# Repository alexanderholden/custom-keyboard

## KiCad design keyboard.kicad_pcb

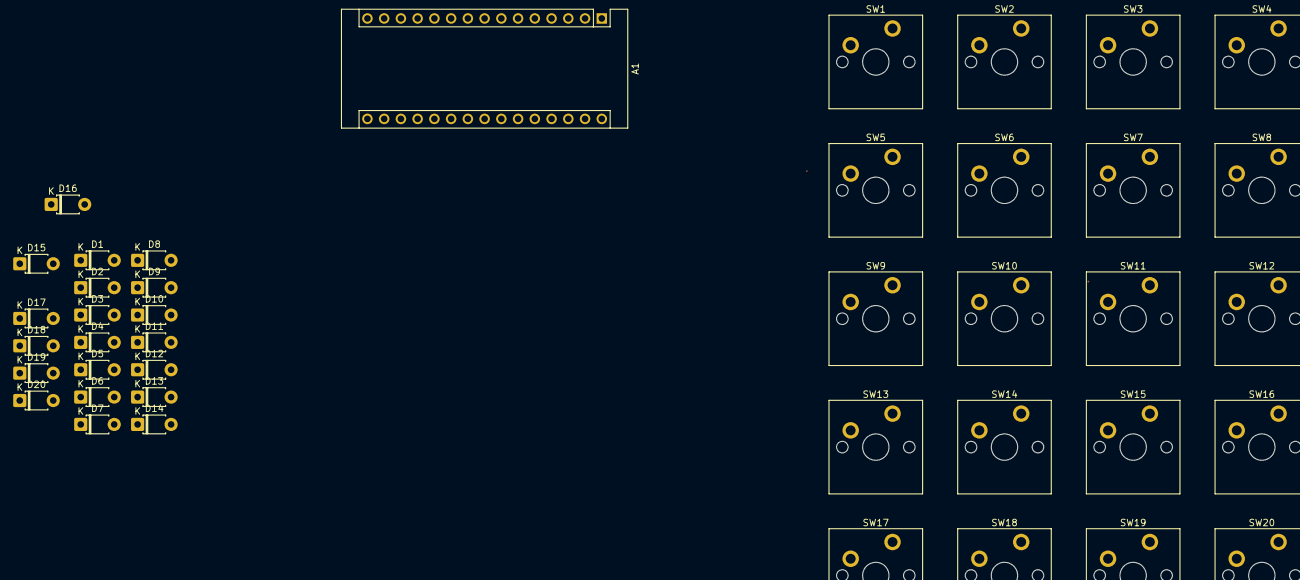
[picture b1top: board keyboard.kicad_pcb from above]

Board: 2 copper layers, 41 parts (0 on the bottom side), 18 nets.

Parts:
A1: Arduino_Nano_v3.x; Arduino_Nano
D1, D2, D3, D4, D5, D6, D7, D8, D9, D10, D11, D12, D13, D14, D15, D16, D17, D18, D19, D20: D; D_T-1_P5.08mm_Horizontal
SW1, SW2, SW3, SW4, SW5, SW6, SW7, SW8, SW9, SW10, SW11, SW12, SW13, SW14, SW15, SW16, SW17, SW18, SW19, SW20: SW_SPST; SW_Cherry_MX_PCB

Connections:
unnamed: D5.2 (A), SW5.2 (B)
unnamed: D6.2 (A), SW6.2 (B)
unnamed: D7.2 (A), SW7.2 (B)
unnamed: D8.2 (A), SW8.2 (B)
unnamed: D9.2 (A), SW9.2 (B)
unnamed: D10.2 (A), SW10.2 (B)
unnamed: D14.1 (K), D18.2 (A), SW18.2 (B)
unnamed: D11.2 (A), SW11.2 (B)
unnamed: D15.1 (K), D19.2 (A), SW19.2 (B)
unnamed: D12.2 (A), SW12.2 (B)
unnamed: D16.2 (A), SW16.2 (B)
unnamed: D13.1 (K), D17.2 (A), SW17.2 (B)
unnamed: D20.2 (A), SW20.2 (B)
unnamed: SW2.1 (A), SW3.1 (A), SW4.1 (A)
unnamed: SW6.1 (A), SW7.1 (A), SW8.1 (A)
unnamed: SW10.1 (A), SW11.1 (A), SW12.1 (A)
unnamed: SW14.1 (A), SW15.1 (A), SW16.1 (A)
unnamed: SW18.1 (A), SW19.1 (A), SW20.1 (A)

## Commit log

2026-03-02 initial
